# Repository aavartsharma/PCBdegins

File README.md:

# PCBdegins
this repo have all my repo desin

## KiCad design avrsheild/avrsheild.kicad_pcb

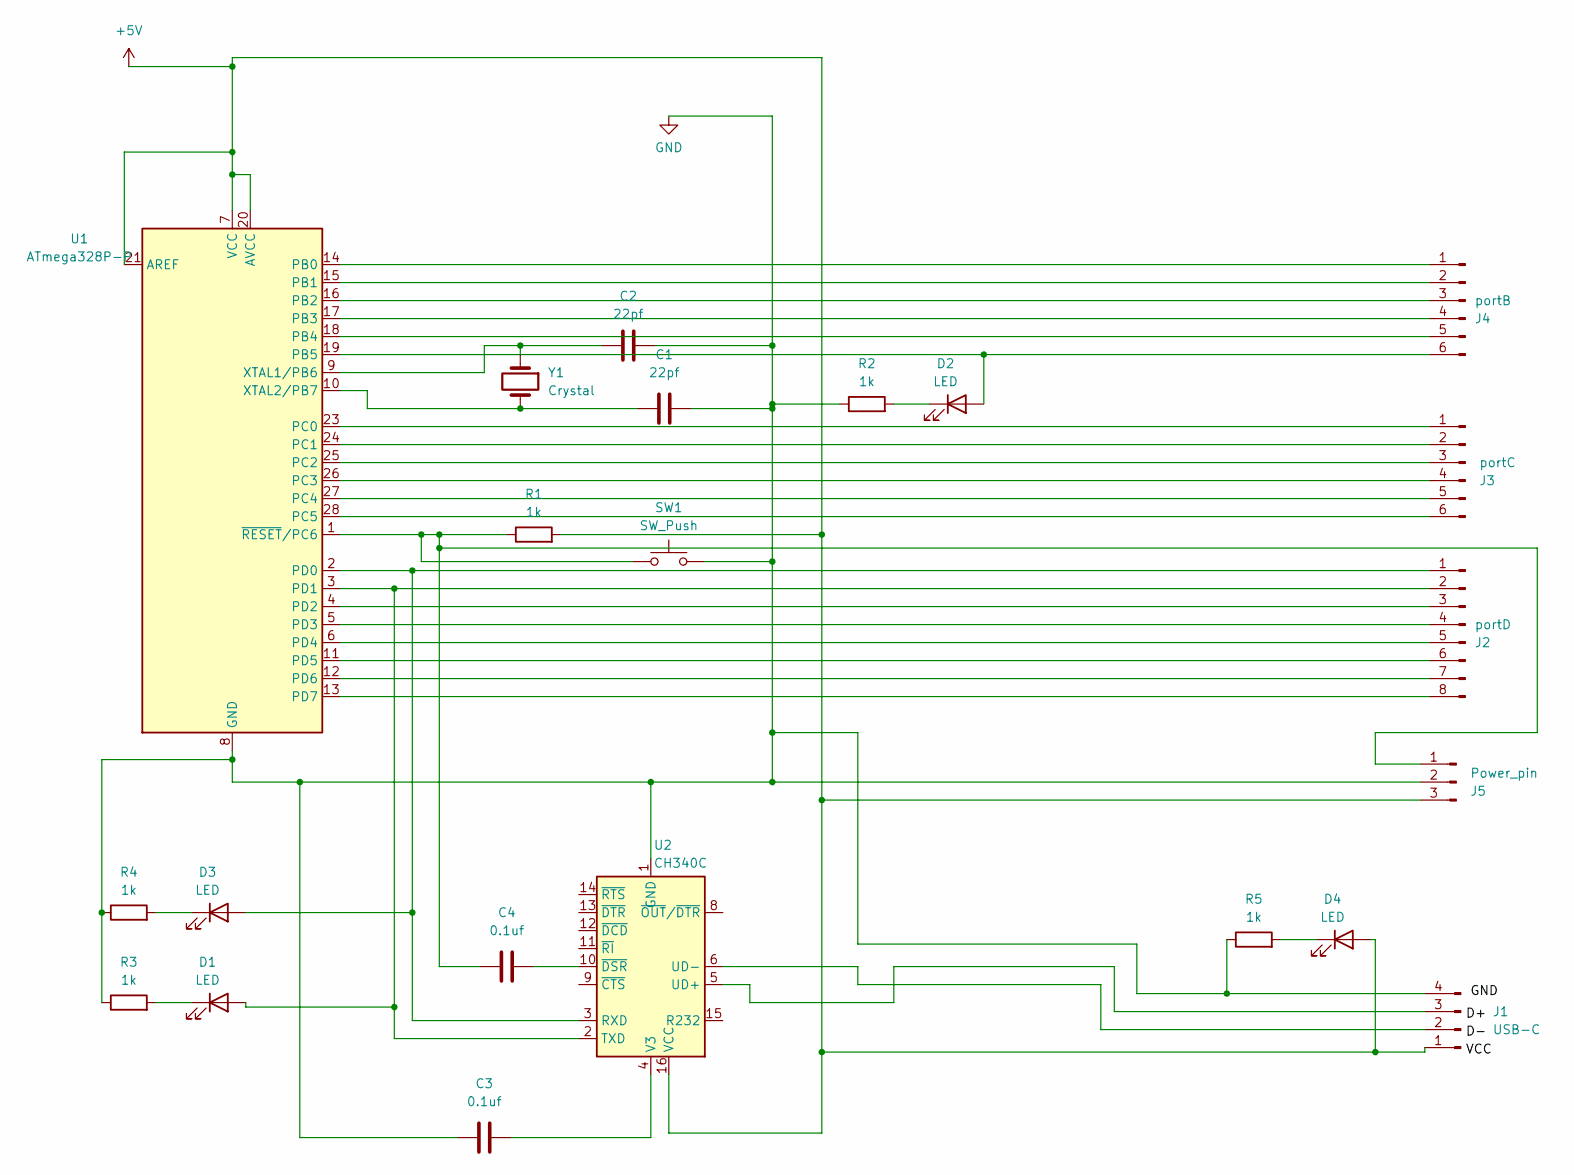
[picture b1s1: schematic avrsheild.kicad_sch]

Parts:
C1, C2: 22pf; C_1206_3216Metric_Pad1.33x1.80mm_HandSolder
C3, C4: 0.1uf; C_1206_3216Metric_Pad1.33x1.80mm_HandSolder
D1, D2, D3, D4: LED; LED_1206_3216Metric_Pad1.42x1.75mm_HandSolder
J1: USB-C; PinHeader_1x04_P2.54mm_Horizontal
J2: portD; PinHeader_1x08_P2.54mm_Horizontal
J3: portC; PinHeader_1x06_P2.54mm_Horizontal
J4: portB; PinHeader_1x06_P2.54mm_Horizontal
J5: Power_pin; PinHeader_1x03_P2.54mm_Horizontal
R1, R2, R3, R4, R5: 1k; R_1206_3216Metric_Pad1.30x1.75mm_HandSolder
SW1: SW_Push; Nidec_Copal_SH-7040B
U1: ATmega328P-P; TQFP-32_7x7mm_P0.8mm
U2: CH340C; SOIC-16_3.9x9.9mm_P1.27mm
Y1: Crystal; Resonator-2Pin_W10.0mm_H5.0mm

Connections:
+5V: D4.2 (A), J1.1, J5.3, R1.2, U1.7 (VCC), U1.20 (AVCC), U1.21 (AREF), U2.16 (VCC)
GND: C1.1, C2.2, C3.2, J1.4, J5.2, R2.1, R3.1, R4.1, R5.1, SW1.2, U1.8 (GND), U1.22 (GND), U2.1 (GND)
unnamed: D1.2 (A), J2.2, U1.3 (PD1), U2.2 (TXD)
unnamed: D1.1 (K), R3.2
unnamed: D2.2 (A), J4.6, U1.19 (PB5)
unnamed: D2.1 (K), R2.2
unnamed: D3.2 (A), J2.1, U1.2 (PD0), U2.3 (RXD)
unnamed: D3.1 (K), R4.2
unnamed: D4.1 (K), R5.2
unnamed: J1.2, U2.6 (UD-)
unnamed: J1.3, U2.5 (UD+)
unnamed: J2.3, U1.4 (PD2)
unnamed: J2.4, U1.5 (PD3)
unnamed: J2.5, U1.6 (PD4)
unnamed: J2.6, U1.11 (PD5)
unnamed: J2.7, U1.12 (PD6)
unnamed: J2.8, U1.13 (PD7)
unnamed: J3.1, U1.23 (PC0)
unnamed: J3.2, U1.24 (PC1)
unnamed: J3.3, U1.25 (PC2)
unnamed: J3.4, U1.26 (PC3)
unnamed: J3.5, U1.27 (PC4)
unnamed: J3.6, U1.28 (PC5)
unnamed: J4.1, U1.14 (PB0)
unnamed: J4.2, U1.15 (PB1)
unnamed: J4.3, U1.16 (PB2)
unnamed: J4.4, U1.17 (PB3)
unnamed: J4.5, U1.18 (PB4)
unnamed: C4.2, J5.1, R1.1, SW1.1, U1.1 (~RESET/PC6)
unnamed: C2.1, U1.9 (XTAL1/PB6), Y1.1
unnamed: C1.2, U1.10 (XTAL2/PB7), Y1.2
unnamed: C3.1, U2.4 (V3)
unnamed: C4.1, U2.10 (~DSR)

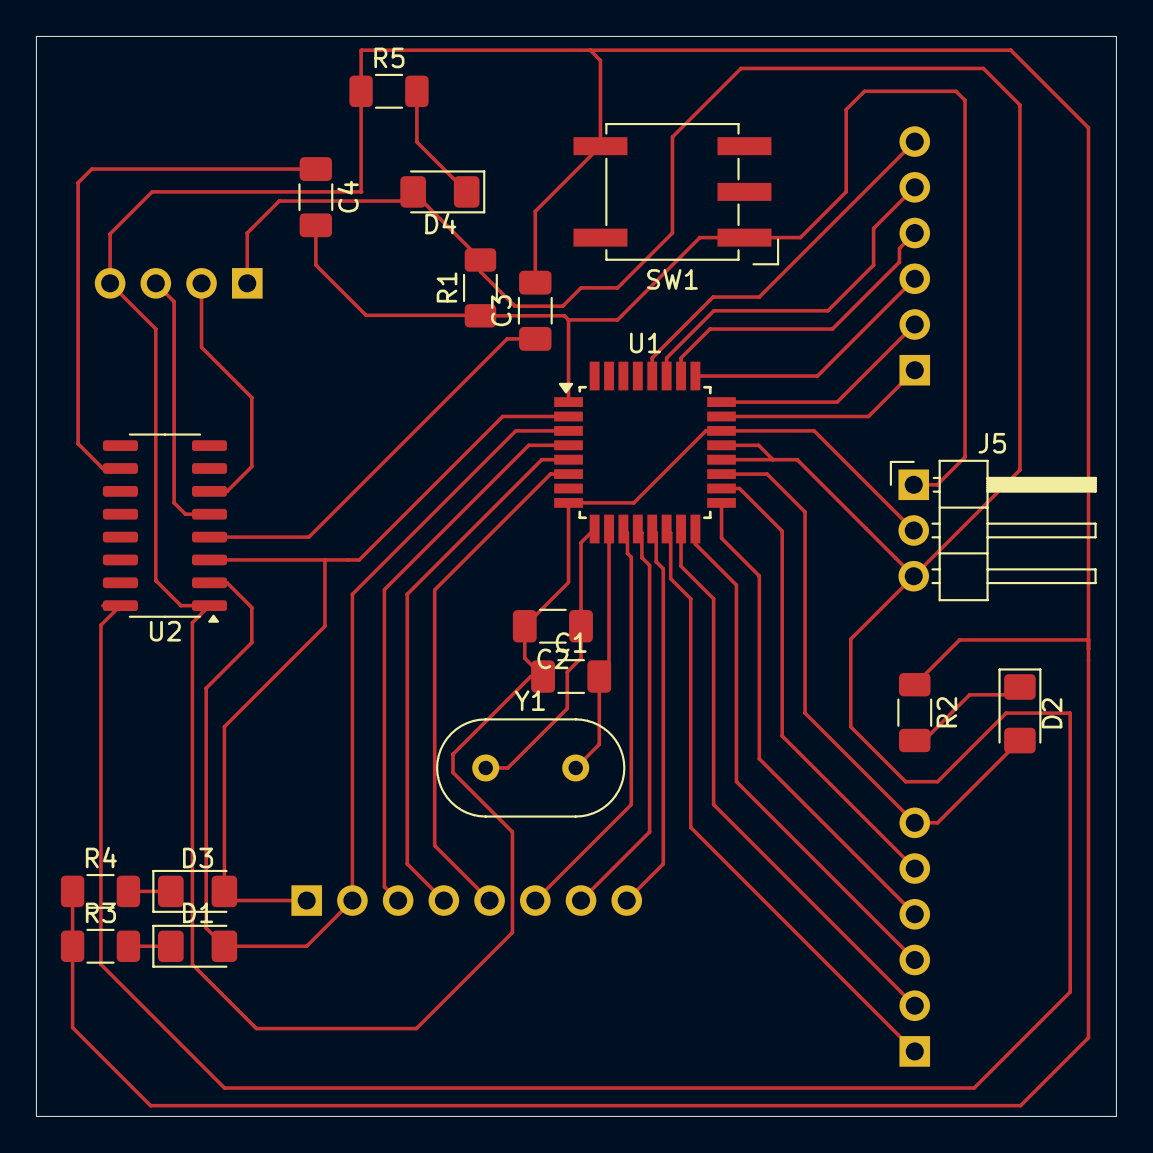
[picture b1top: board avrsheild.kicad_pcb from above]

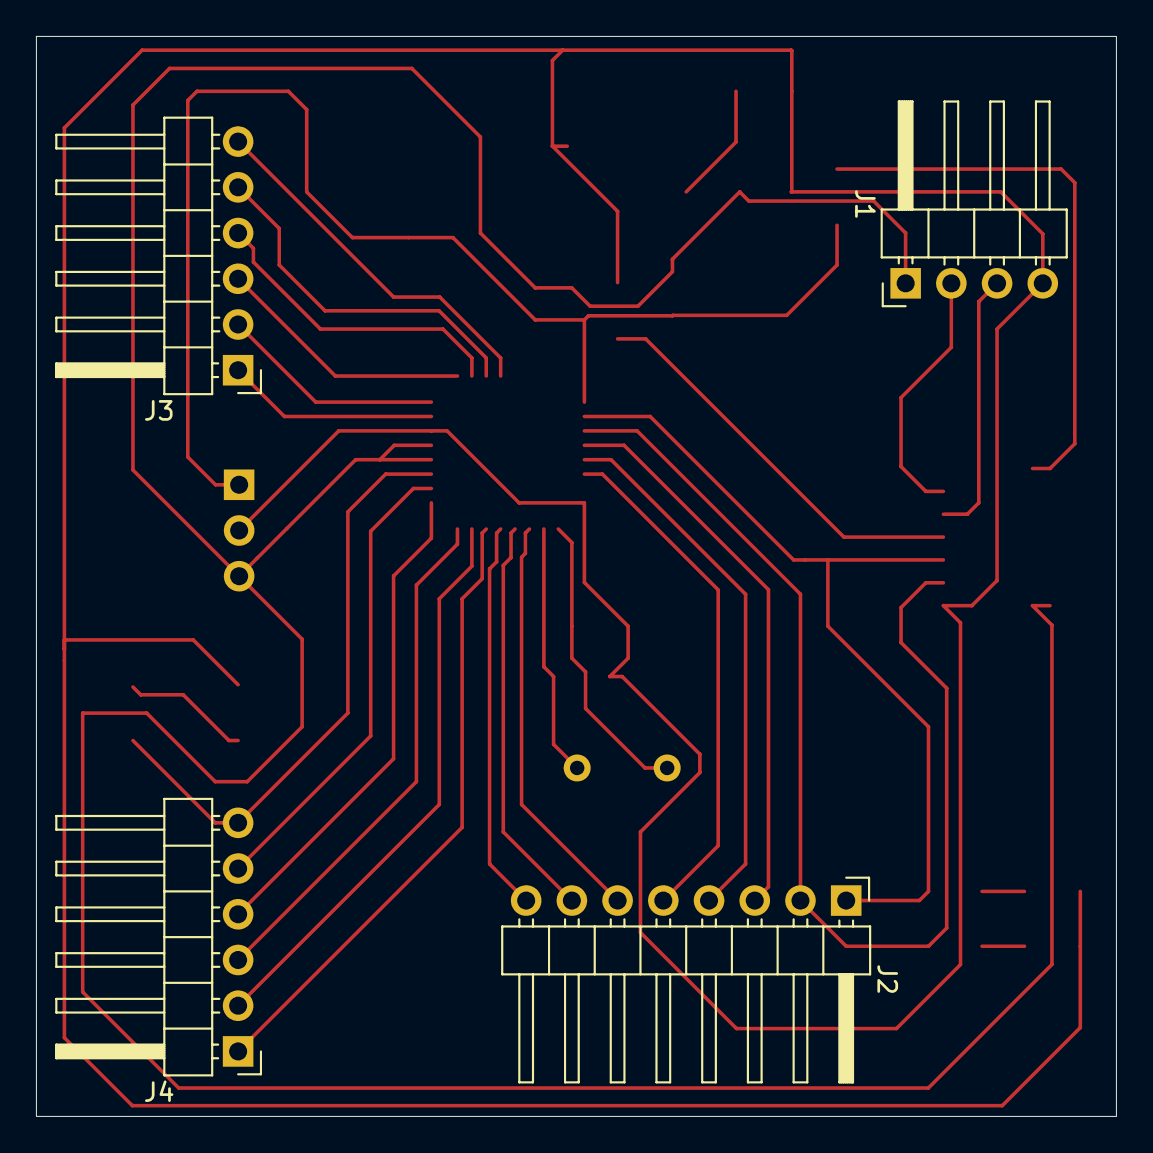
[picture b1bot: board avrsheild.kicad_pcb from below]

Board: 2 copper layers, 60.0 x 60.0 mm, 22 parts (4 on the bottom side), 33 nets.

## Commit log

2025-08-29 inital comit with degins of avrsheild
2025-08-30 PCB layout is done
